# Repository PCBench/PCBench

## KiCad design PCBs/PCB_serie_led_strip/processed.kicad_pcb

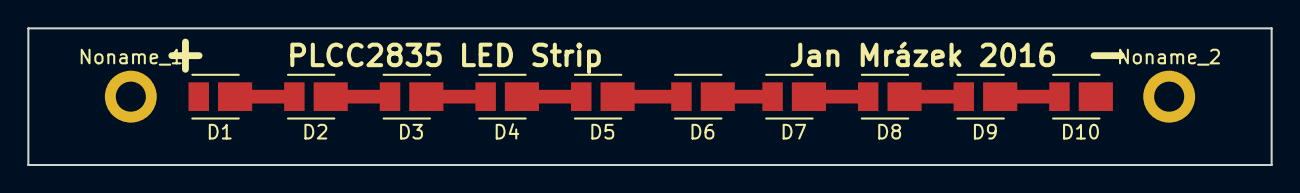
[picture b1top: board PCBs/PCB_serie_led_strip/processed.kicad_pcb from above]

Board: 2 copper layers, 91.0 x 10.0 mm, 12 parts (0 on the bottom side), 9 nets.

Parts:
D1, D2, D3, D4, D5, D6, D7, D8, D9, D10: LED; LED_PLCC_2835_Handsolder
Noname_1, Noname_2: MountingHole_2.2mm_M2_DIN965_Pad

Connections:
unnamed: D1.1, D2.2
unnamed: D2.1, D3.2
unnamed: D3.1, D4.2
unnamed: D4.1, D5.2
unnamed: D5.1, D6.2
unnamed: D6.1, D7.2
unnamed: D7.1, D8.2
unnamed: D8.1, D9.2
unnamed: D9.1, D10.2

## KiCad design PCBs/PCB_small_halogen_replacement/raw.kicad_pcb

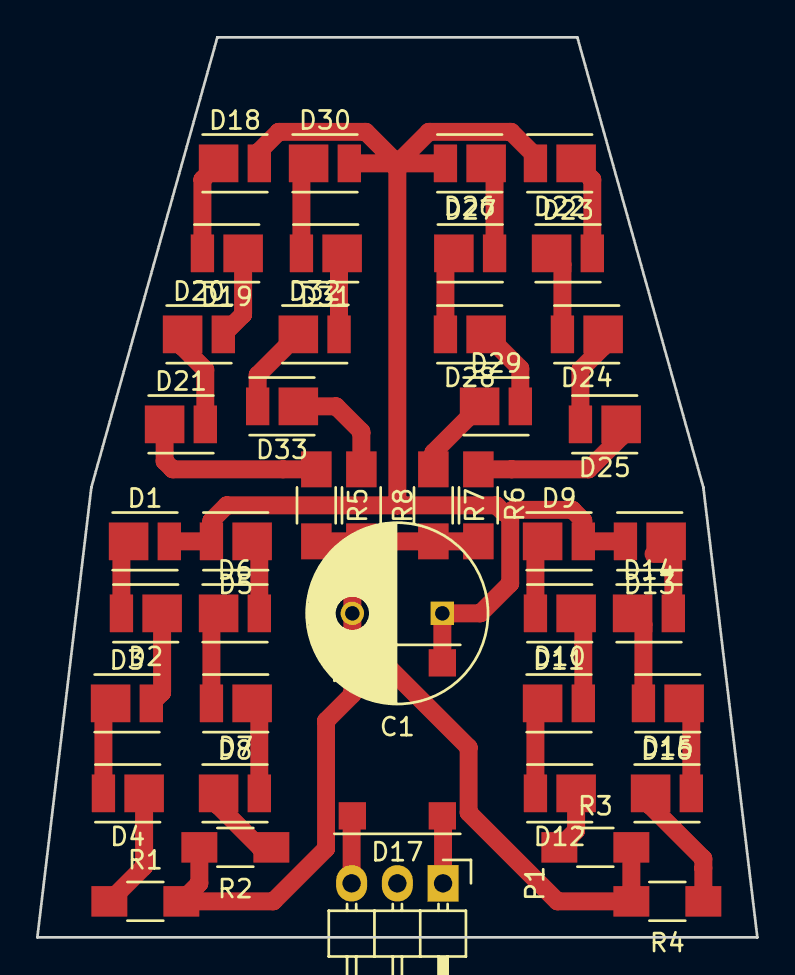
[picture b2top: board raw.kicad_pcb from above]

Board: 2 copper layers, 40.0 x 50.0 mm, 43 parts (0 on the bottom side), 36 nets.

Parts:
C1: CP; C_Radial_D10_L13_P5
D1, D2, D3, D4, D5, D6, D7, D8, D9, D10, D11, D12, D13, D14, D15, D16, D18, D19, D20, D21, D22, D23, D24, D25, D26, D27, D28, D29, D30, D31, D32, D33: LED; LED_PLCC_2835
D17: DB207S
P1: CONN_01X03; Pin_Header_Angled_1x03
R1, R2, R3, R4, R5, R6, R7, R8: 47R; R_1206_HandSoldering

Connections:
GND: C1.2, D17.1, R1.2, R2.2, R3.2, R4.2, R5.2, R6.2, R7.2, R8.2
unnamed: D1.1, D2.2
unnamed: D2.1, D3.2
unnamed: D3.1, D4.2
unnamed: D4.1, R1.1
unnamed: D5.1, D6.2
unnamed: D6.1, D7.2
unnamed: D7.1, D8.2
unnamed: D8.1, R2.1
unnamed: D10.1, D11.2
unnamed: D9.1, D10.2
unnamed: D11.1, D12.2
unnamed: D12.1, R3.1
unnamed: D13.1, D14.2
unnamed: D14.1, D15.2
unnamed: D15.1, D16.2
unnamed: D16.1, R4.1
unnamed: D17.2, P1.3
unnamed: D17.4, P1.1
unnamed: D18.1, D19.2
unnamed: D19.1, D20.2
unnamed: D20.1, D21.2
unnamed: D21.1, R5.1
unnamed: D22.1, D23.2
unnamed: D23.1, D24.2
unnamed: D24.1, D25.2
unnamed: D25.1, R6.1
unnamed: D26.1, D27.2
unnamed: D27.1, D28.2
unnamed: D28.1, D29.2
unnamed: D29.1, R7.1
unnamed: D30.1, D31.2
unnamed: D31.1, D32.2
unnamed: D32.1, D33.2
unnamed: D33.1, R8.1
VCC: C1.1, D1.2, D5.2, D9.2, D13.2, D17.3, D18.2, D22.2, D26.2, D30.2

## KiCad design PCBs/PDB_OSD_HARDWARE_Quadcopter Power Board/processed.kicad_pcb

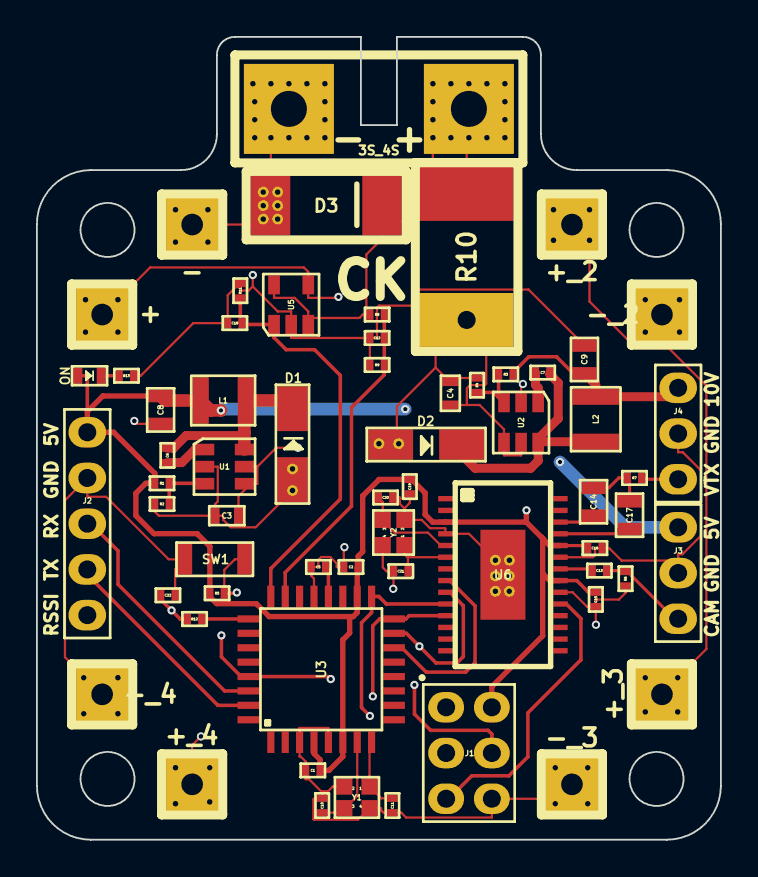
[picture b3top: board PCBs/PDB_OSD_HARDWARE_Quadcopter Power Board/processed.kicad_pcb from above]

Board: 4 copper layers, 38.0 x 44.6 mm, 62 parts (0 on the bottom side), 34 nets.

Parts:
3S_4S: CONNECTOR_LIPO; SolderPad-2_5mm
+: ESC1_V+; SolderPad-1_3mm
+_2: ESC4_V+; SolderPad-1_3mm
+_3: ESC3_V+; SolderPad-1_3mm
+_4: ESC2_V+; SolderPad-1_3mm
-: ESC1_GND; SolderPad-1_3mm
-_2: ESC4_GND; SolderPad-1_3mm
-_3: ESC3_GND; SolderPad-1_3mm
-_4: ESC2_GND; SolderPad-1_3mm
C1, C2, C5, C12, C13, C15, C16, C18, C19: 100nF; SMD_0402
C3, C4: 10uF; SMD_0603
C6, C7: 10nF; SMD_0402
C8, C9: 22uF; SMD_0805
C10, C11, C20, C21: 15pF; SMD_0402
C14, C17: 47uF; SMD_0805
C22: 1uF; SMD_0402
D1, D2: B230A; Diode_B230A
D3: 5.0SMDJ17CA
J1: ICSP; PinHeader_2x3-2.54mm
J2: Connector_01x05; PinHeader_1x5-2.54mm
J3: CAMERA; PinHeader_1x3-2.54mm
J4: VTX; PinHeader_1x3-2.54mm
L1, L2: 4.7uH; SMD_1210
ON: PWR_LED; Diode_0603
R1: 51.1K; SMD_0402
R2, R4, R8, R12: 10K; SMD_0402
R3: 113K; SMD_0402
R5, R9, R13: 1K; SMD_0402
R6, R7: 75; SMD_0402
R10: 0.5m; SMD_3920
R11: 36.5K; SMD_0402
SW1: ResetButton; Button_B3U-1000P
U1, U2: AP3211; SOT23-6
U3: ATMEGA328P-AU; TQFP32_7x7mm_Pitch0.8mm
U5: INA169; SOT23-5
U6: MAX7456; SSOP28-1EXP_5.3x10.2mm_Pitch0.65mm
Y1: 16MHz; Crystal_2mm-1.6mm
Y2: 27MHz; Crystal_2mm-1.6mm

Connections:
+5V: C1.1, C2.1, C8.1, C15.1, C16.1, C19.2, J1.2, J2.1, J3.1, L1.2, ON.2, R1.1, R5.1, U3.4, U3.6, U3.18, U6.3, U6.21, U6.24
+10V: C9.1, J4.1, L2.2, R3.1
CURRENT_ADC: C18.1, R11.1, U3.24, U5.1
GND: 3S_4S.2, -.1, -_2.1, -_3.1, -_4.1, C1.2, C2.2, C3.2, C4.2, C5.2, C8.2, C9.2, C10.1, C11.1, C12.2, C15.2, C16.2, C18.2, C19.1, C20.1, C21.1, C22.2, D1.2, D2.2, D3.2, J1.6, J2.2, J3.2, J4.2, R2.2, R4.2, R6.2, R9.2, R11.2, R13.2, SW1.2, U1.2, U2.2, U3.3, U3.5, U3.21, U5.2, U6.4, U6.20, U6.23, U6.29, Y1.2, Y1.4, Y2.2, Y2.4
LIPO_ADC: C12.1, R8.2, R9.1, U3.23
LIPO_IN: 3S_4S.1, D3.1, R8.1, R10.1, U5.3, U5.5
LIPO_IN2: +.1, +_2.1, +_3.1, +_4.1, C3.1, C4.1, R10.2, U1.4, U1.5, U2.4, U2.5, U5.4
unnamed: C5.1, U3.20
unnamed: C6.1, U1.1
unnamed: C6.2, D1.1, L1.1, U1.6
unnamed: C7.1, U2.1
unnamed: C7.2, D2.1, L2.1, U2.6
unnamed: C10.2, U3.7, Y1.3
unnamed: C11.2, U3.8, Y1.1
unnamed: C13.1, U6.22
unnamed: C14.1, U6.26
unnamed: C14.2, C17.2, R7.1
unnamed: C17.1, U6.25
unnamed: C20.2, U6.5, Y2.3
unnamed: C21.2, U6.6, Y2.1
unnamed: ON.1, R13.1
unnamed: R1.2, R2.1, U1.3
unnamed: R3.2, R4.1, U2.3
unnamed: R12.1, U3.25
OSD_CS: U3.14, U6.8
RESET: J1.5, R5.2, SW1.1, U3.29, U6.19
RSSI: C22.1, J2.5, R12.2
RX: J2.3, U3.30
SPI_MISO: J1.1, U3.16, U6.11
SPI_MOSI: J1.4, U3.15, U6.9
SPI_SCK: J1.3, U3.17, U6.10
TX: J2.4, U3.31
VIDEO_IN: C13.2, J3.3, R6.1
VIDEO_OUT: J4.3, R7.2

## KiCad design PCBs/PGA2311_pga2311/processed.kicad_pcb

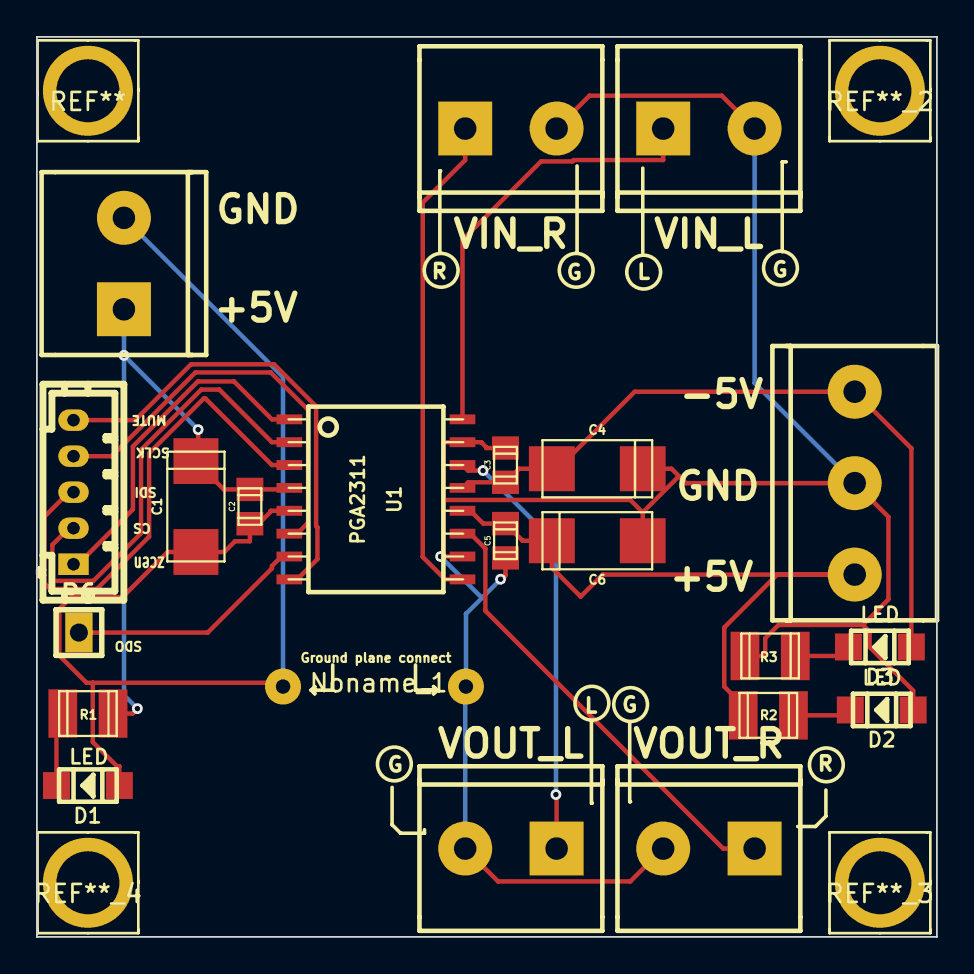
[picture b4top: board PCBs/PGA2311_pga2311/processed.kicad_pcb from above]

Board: 2 copper layers, 50.0 x 50.0 mm, 22 parts (0 on the bottom side), 18 nets.

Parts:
C1, C4, C6: 10uF; c_tant_C
C2, C3, C5: 0.1uF; c_0805
D1, D2, D3: LED; Led_1206
Noname_1: JUMPER; WireConnection_0-8mmDrill
P1: VIN_R; mors_2p
P2: VOUT_R; mors_2p
P3: VIN_L; mors_2p
P4: VOUT_L; mors_2p
P5: b5b-ph-kl
P6: SDO_TO_OTHER_PGA2311; pin_strip_1
P7: mors_3p_inv_pins
P8: mors_2p
R1, R2, R3: 10k; r_1210
U1: PGA2311; soic-16

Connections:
+5V: C5.1, C6.1, P7.1, R2.1, U1.12
+5VD: C1.1, C2.1, P8.1, R1.2, U1.4
-5V: C3.2, C4.2, D3.1, P7.3, U1.13
CS: P5.2, U1.2
GND_A: C3.1, C4.1, C5.2, C6.2, D2.1, Noname_1.1, P1.2, P2.2, P3.2, P4.2, P7.2, R3.1, U1.10, U1.15
GND_D: C1.2, C2.2, D1.1, Noname_1.2, P8.2, U1.5
MUTE: P5.5, U1.8
unnamed: D1.2, R1.1
unnamed: D2.2, R2.2
unnamed: D3.2, R3.2
SCLK: P5.4, U1.6
SDI: P5.3, U1.3
SDO: P6.1, U1.7
VIN_L: P3.1, U1.16
VIN_R: P1.1, U1.9
VOUT_L: P4.1, U1.14
VOUT_R: P2.1, U1.11
ZCEN: P5.1, U1.1

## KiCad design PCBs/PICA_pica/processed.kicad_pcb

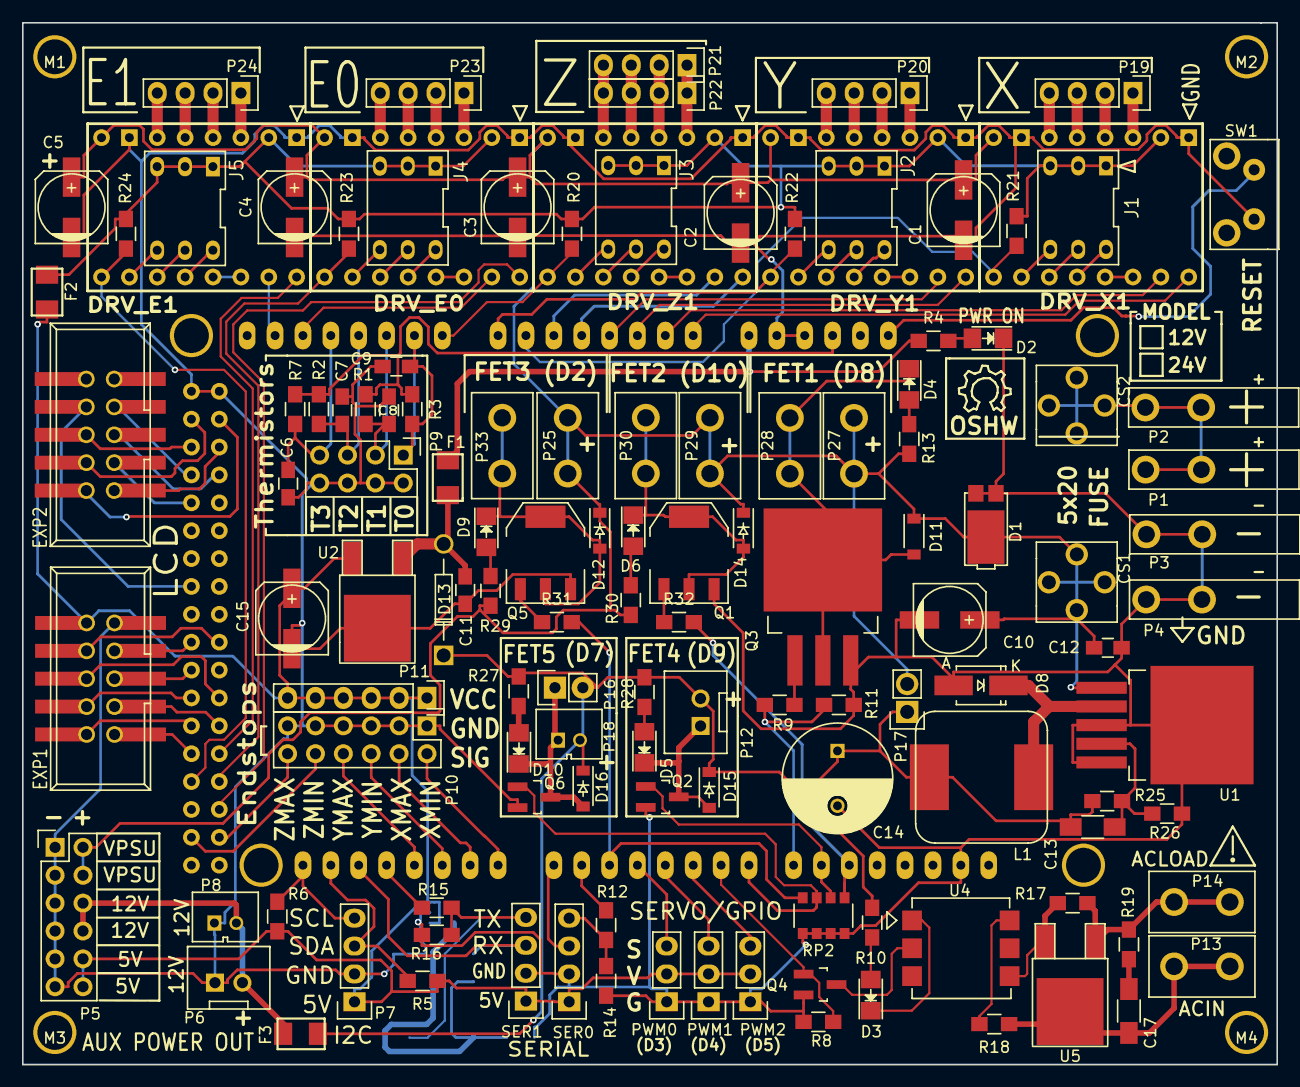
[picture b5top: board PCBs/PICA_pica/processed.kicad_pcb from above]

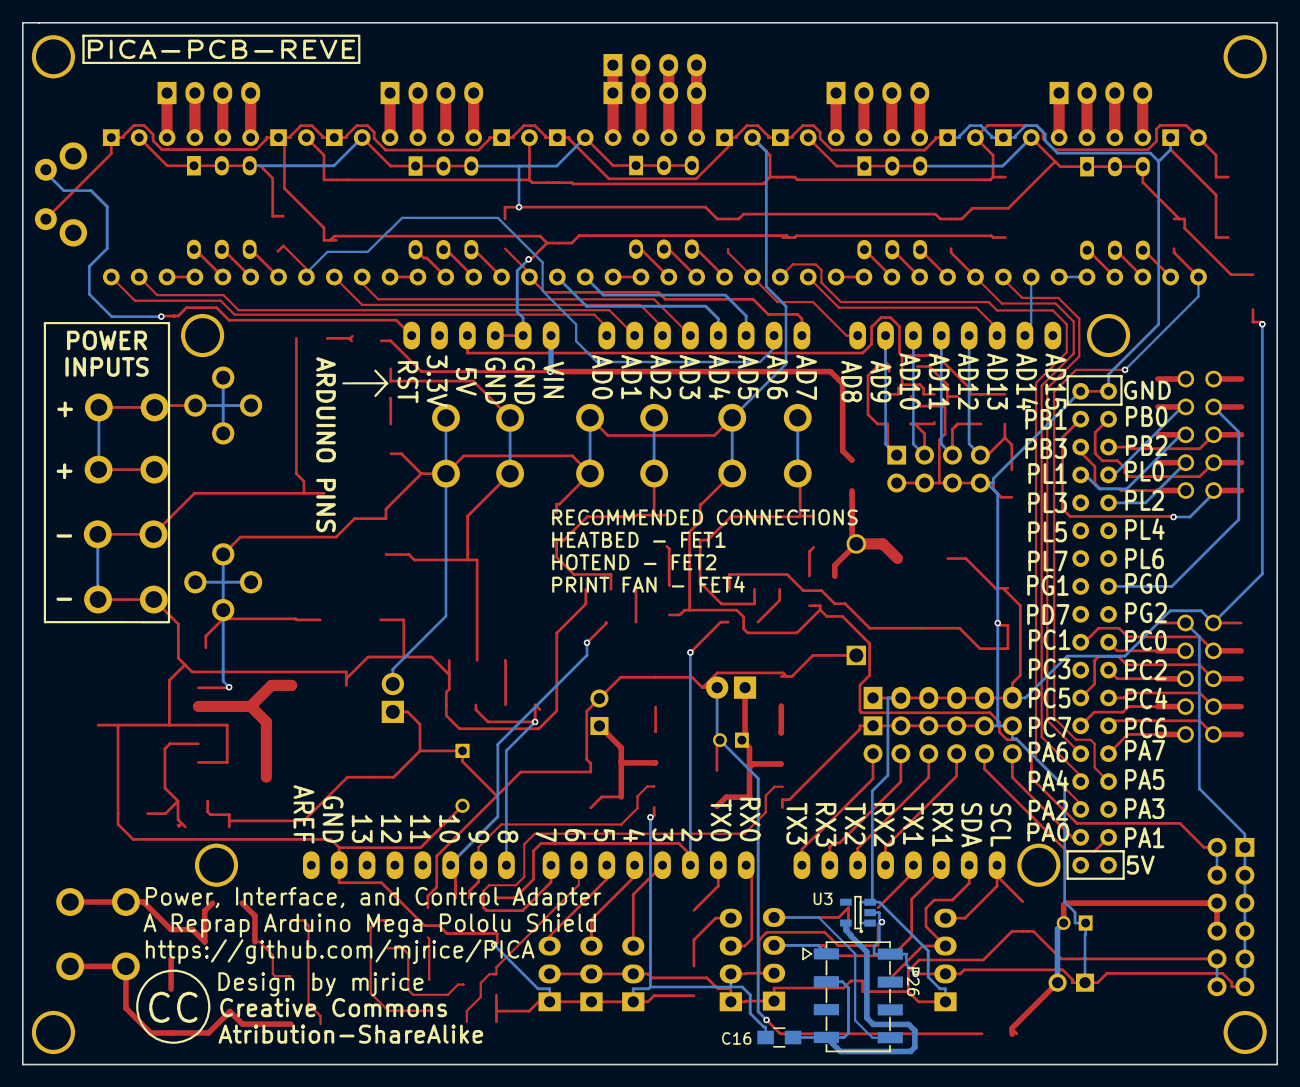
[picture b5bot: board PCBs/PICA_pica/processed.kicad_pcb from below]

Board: 2 copper layers, 114.3 x 94.9 mm, 135 parts (3 on the bottom side), 134 nets.

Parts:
C1, C2, C3, C4, C5, C10, C15: 100UF; c_elec_6.3x5.8
C6, C7, C8, C9, C11, C12, C16: .1UF; C_0805_HandSoldering
C13, C17: 10nF; C_1206_HandSoldering
C14: 470u; C_Radial_D10_L13_P5
CS1, CS2: FUSE_CLIP_5x20; FUSE_CLIP_D_5x20
D1: SBRT20M60SP5-7; POWERDI5
D2: GREEN; LED_1206
D3, D4, D5, D6, D9, D10: Led_Small; LED_1206
D8: MBRA340T3G; SMA_Handsoldering
D11, D12, D14, D15, D16: MBR0560; SOD-123
D13: 1N5333; Diode_Horizontal
DRV_E0, DRV_E1: POLOLU_A4988; SWDIP8_.6W
DRV_X1: POLOLU_A4988; SWDIP8_.6W
DRV_Y1: POLOLU_A4988; SWDIP8_.6W
DRV_Z1: POLOLU_A4988; SWDIP8_.6W
EXP1, EXP2: CONN_02X05; IDC_Header_Straight_10pins_DUAL
F1, F2, F3: 0ZCJ0020FF2E; Fuse_SMD1206_Wave
J1, J2, J3, J4, J5: CONN_02X03; DIP-6_0_ELL
L1: 82uH; RH127
M1, M2, M3, M4: CONN_01X01; MHOLE125
P1, P2, P3, P4: 36-4966-ND; SPADE_CONN_RT
P5, P10: CONN_02X06; Pin_Header_Straight_2x06
P6, P12: JST-XH; JST_XH_2POS
P7, P19, P20, P21, P22, P23, P24: CONN_01X04; Pin_Header_Straight_1x04
P8, P18: JST-PH; JST_PH_2POS
P9: CONN_02X04; Pin_Header_Straight_2x04
P11: CONN_01X06; Pin_Header_Straight_1x06
P13, P14, P25, P27, P28, P29, P30, P33: CONN_01X02; SPACE_CONN_VERT
P16: DUPONT; Pin_Header_Straight_1x02
P17: CONN_01X02; Pin_Header_Straight_1x02
P26: CONN_02X04; PINHEADER_2X4_SMD
PWM0, PWM1, PWM2: CONN_01X03; Pin_Header_Straight_1x03
Q1, Q5: IRFL024ZPbF; SOT-223
Q2, Q4, Q6: IRLML6346; SOT-23_Handsoldering
Q3: IRFZ48VS; TO-263-3Lead
R1, R2, R3, R4, R5, R6, R7, R13, R14, R16, R20, R21, R22, R23, R24, R27, R28, R29, R30: 4.7K; R_0805_HandSoldering
R8, R11: 100K; R_0805_HandSoldering
R9, R19, R31, R32: 50; R_0805_HandSoldering
R10: 200; R_0805_HandSoldering
R12, R15, R26: 2K; R_0805_HandSoldering
R17, R18: 360; R_0805_HandSoldering
R25: 17.2K; R_0805_HandSoldering
RP2: YC164-JR-07150KL; RESARY_4_CTS_744
SER0, SER1: CONN_01X04; Pin_Header_Straight_1x04
SHIELD1: ARDUINO_MEGA_SHIELD; MEGA_NOLINES
SW1: BSF-3100; BSF_RT
U1: LM2596-ADJ; TO-263-5Lead
U2: MC7805BDTRKG; TO-252-2Lead
U3: TLV70033DDC; SOT-23-5
U4: MOC3061M; 6SMD
U5: TRIAC; TO-252-2Lead

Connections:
+5VL: R1.1, R2.1, R3.1, R7.1, SHIELD1.5V
+12V: C13.1, C14.1, D13.1, D15.1, D16.1, F3.2, L1.2, P12.2, P16.2, P17.1, P18.2, R10.1, R25.1, R27.2, R28.2
+VPSU: C1.1, C2.1, C3.1, C4.1, C5.1, C10.1, C12.1, CS1.1, CS1.2, D1.3, D11.1, D12.1, D14.1, DRV_E0.8, DRV_E1.8, DRV_X1.8, DRV_Y1.8, DRV_Z1.8, P5.2, P5.4, P17.2, P25.1, P25.2, P27.1, P27.2, P29.1, P29.2, R13.1, R29.2, R30.2, U1.1
/AM_VIN: C11.1, D13.2, F1.1, U2.1
/DRV_VCC: DRV_E0.2, DRV_E1.2, DRV_X1.2, DRV_Y1.2, DRV_Z1.2, F2.1, J1.1, J1.3, J1.5, J2.1, J2.3, J2.5, J3.1, J3.3, J3.5, J4.1, J4.3, J4.5, J5.1, J5.3, J5.5, R20.1, R21.1, R22.1, R23.1, R24.1
/FB_ADJ: C13.2, R25.2, R26.1, U1.4
/FE1_D: D5.1, D15.2, P12.1, Q2.3
/FE2_D: D10.1, D16.2, P16.1, P18.1, Q6.3
/HE1_D: D6.1, D14.2, P30.1, P30.2, Q1.2, Q1.4
/HE1_G: Q1.1, R32.1
/HE2_D: D9.1, D12.2, P33.1, P33.2, Q5.2, Q5.4
/HE2_G: Q5.1, R31.1
/MISO: EXP2.1, SHIELD1.50
/MOSI: EXP2.6, SHIELD1.51
/Q3_D: D4.1, D11.2, P28.1, P28.2, Q3.2, Q3.4
/SCK: EXP2.2, SHIELD1.52
/SDSS: EXP2.4, SHIELD1.53
/SD_CARD_DET: EXP2.7, SHIELD1.49
/TX1_S: P26.8, R15.1, R16.1, SER1.4
/VAA_IN: CS2.1, CS2.2, P1.1, P1.2, P2.1, P2.2
BED_EN: R9.2, R11.1, SHIELD1.8
BTN_EN1: EXP2.3, SHIELD1.47
BTN_EN2: EXP2.5, SHIELD1.48
BTN_ENC: EXP1.2, SHIELD1.31
E0_DIR: DRV_E0.16, SHIELD1.24
E0_EN: DRV_E0.9, R23.2, SHIELD1.26
E0_STEP: DRV_E0.15, SHIELD1.AD13
E1_DIR: DRV_E1.16, SHIELD1.28
E1_EN: DRV_E1.9, R24.2, SHIELD1.27
E1_STEP: DRV_E1.15, SHIELD1.AD14
FAN2_EN: Q6.1, RP2.3, SHIELD1.7
FAN_EN: Q2.1, RP2.2, SHIELD1.9
GND: C1.2, C2.2, C3.2, C4.2, C5.2, C6.2, C7.2, C8.2, C9.2, C10.2, C11.2, C12.2, C14.2, C15.2, C16.2, D1.1, D1.2, D2.1, D8.2, DRV_E0.1, DRV_E0.7, DRV_E1.1, DRV_E1.7, DRV_X1.1, DRV_X1.7, DRV_Y1.1, DRV_Y1.7, DRV_Z1.1, DRV_Z1.7, EXP1.9, P3.1, P3.2, P4.1, P4.2, P5.1, P5.3, P5.5, P5.7, P5.9, P5.11, P6.1, P7.2, P8.1, P9.2, P9.4, P9.6, P9.8, P10.1, P10.3, P10.5, P10.7, P10.9, P10.11, P26.2, PWM0.1, PWM1.1, PWM2.1, Q1.3, Q2.2, Q3.3, Q4.2, Q5.3, Q6.2, R8.2, R11.2, R14.2, R16.2, R26.2, RP2.5, RP2.6, RP2.7, RP2.8, SER0.2, SER1.2, SHIELD1.GND1, SHIELD1.GND2, SHIELD1.GND3, SHIELD1.GND4, SHIELD1.GND5, SW1.1, U1.3, U1.5, U2.2, U3.2
HOTEND2_EN: R31.2, RP2.4, SHIELD1.2
HOTEND_EN: R32.2, RP2.1, SHIELD1.10
KILL_PIN: EXP2.8, SHIELD1.41
LCD_BEEPER: EXP1.1, SHIELD1.29
LCD_D4: EXP1.5, SHIELD1.35
LCD_D5: EXP1.6, SHIELD1.32
LCD_D6: EXP1.7, SHIELD1.37
LCD_D7: EXP1.8, SHIELD1.36
LCD_EN: EXP1.3, SHIELD1.30
LCD_RS: EXP1.4, SHIELD1.33
unnamed: C16.1, P26.3, P26.7, U3.5
unnamed: C17.1, P13.1, P13.2, R18.1, U5.2
unnamed: C17.2, R19.1
unnamed: D2.2, R4.2
unnamed: D3.1, U4.1
unnamed: D3.2, R10.2
unnamed: D4.2, R13.2
unnamed: D5.2, R28.1
unnamed: D6.2, R30.1
unnamed: D8.1, L1.1, U1.2
unnamed: D9.2, R29.1
unnamed: D10.2, R27.1
unnamed: DRV_E0.3, P23.1
unnamed: DRV_E0.4, P23.2
unnamed: DRV_E0.5, P23.3
unnamed: DRV_E0.6, P23.4
unnamed: DRV_E0.10, J4.6
unnamed: DRV_E0.11, J4.4
unnamed: DRV_E0.12, J4.2
unnamed: DRV_E0.13, DRV_E0.14
unnamed: DRV_E1.3, P24.1
unnamed: DRV_E1.4, P24.2
unnamed: DRV_E1.5, P24.3
unnamed: DRV_E1.6, P24.4
unnamed: DRV_E1.10, J5.6
unnamed: DRV_E1.11, J5.4
unnamed: DRV_E1.12, J5.2
unnamed: DRV_E1.13, DRV_E1.14
unnamed: DRV_X1.3, P19.1
unnamed: DRV_X1.4, P19.2
unnamed: DRV_X1.5, P19.3
unnamed: DRV_X1.6, P19.4
unnamed: DRV_X1.10, J1.6
unnamed: DRV_X1.11, J1.4
unnamed: DRV_X1.12, J1.2
unnamed: DRV_X1.13, DRV_X1.14
unnamed: DRV_Y1.3, P20.1
unnamed: DRV_Y1.4, P20.2
unnamed: DRV_Y1.5, P20.3
unnamed: DRV_Y1.6, P20.4
unnamed: DRV_Y1.10, J2.6
unnamed: DRV_Y1.11, J2.4
unnamed: DRV_Y1.12, J2.2
unnamed: DRV_Y1.13, DRV_Y1.14
unnamed: DRV_Z1.3, P21.1, P22.1
unnamed: DRV_Z1.4, P21.2, P22.2
unnamed: DRV_Z1.5, P21.3, P22.3
unnamed: DRV_Z1.6, P21.4, P22.4
unnamed: DRV_Z1.10, J3.6
unnamed: DRV_Z1.11, J3.4
unnamed: DRV_Z1.12, J3.2
unnamed: DRV_Z1.13, DRV_Z1.14
unnamed: F1.2, R4.1, SHIELD1.V_IN
unnamed: F3.1, P5.6, P5.8, P6.2, P8.2
unnamed: P14.1, P14.2, R17.2, R19.2, U5.1
unnamed: Q3.1, R9.1
unnamed: Q4.3, U4.2
unnamed: R12.1, R14.1, SER0.4
unnamed: R17.1, U4.4, U5.3
unnamed: R18.2, U4.6
unnamed: SHIELD1.RST, SW1.2
PWM0: PWM0.3, SHIELD1.3
PWM1: PWM1.3, SHIELD1.4
PWM2: PWM2.3, SHIELD1.5
RX0: SER0.3, SHIELD1.0
RX1: P26.1, SER1.3, SHIELD1.19
SCL: P7.4, R6.2, SHIELD1.21
SDA: P7.3, R5.2, SHIELD1.20
SSR_EN: Q4.1, R8.1, SHIELD1.6
THERM0: C9.1, P9.1, R3.2, SHIELD1.AD9
THERM1: C8.1, P9.3, R1.2, SHIELD1.AD10
THERM2: C7.1, P9.5, R2.2, SHIELD1.AD11
THERM3: C6.1, P9.7, R7.2, SHIELD1.AD12
TX0: R12.2, SHIELD1.1
TX1: R15.2, SHIELD1.18
VCC: C15.1, EXP1.10, F2.2, P5.10, P5.12, P7.1, P11.1, P11.2, P11.3, P11.4, P11.5, P11.6, PWM0.2, PWM1.2, PWM2.2, R5.1, R6.1, SER0.1, SER1.1, U2.3, U3.1, U3.3
X_DIR: DRV_X1.16, SHIELD1.AD0
X_EN: DRV_X1.9, R21.2, SHIELD1.AD6
X_MAX: P10.4, SHIELD1.15
X_MIN: P10.2, SHIELD1.14
X_STEP: DRV_X1.15, SHIELD1.AD1
Y_DIR: DRV_Y1.16, SHIELD1.AD2
Y_EN: DRV_Y1.9, R22.2, SHIELD1.AD7
Y_MAX: P10.8, SHIELD1.17
Y_MIN: P10.6, SHIELD1.16
Y_STEP: DRV_Y1.15, SHIELD1.AD3
Z_DIR: DRV_Z1.16, SHIELD1.AD4
Z_EN: DRV_Z1.9, R20.2, SHIELD1.AD8
Z_MAX: P10.12, SHIELD1.22
Z_MIN: P10.10, SHIELD1.23
Z_STEP: DRV_Z1.15, SHIELD1.AD5

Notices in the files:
PCBs/PICA_pica/processed.kicad_pcb:
Creative Commons
Atribution-ShareAlike
